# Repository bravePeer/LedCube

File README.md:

# LedCube
My version of Led Cube 5x5x5.

## Features:

| Name                     | Progress |
| :--:                     | :------: |
| animated letter          | in progress  |
| animation "droping leds" | in progress |
| animation with music     | planned |
| clock                    | planned |
| communication with PC    | in progress |

⚠️ Now all code is written to 5x5 led matrix.

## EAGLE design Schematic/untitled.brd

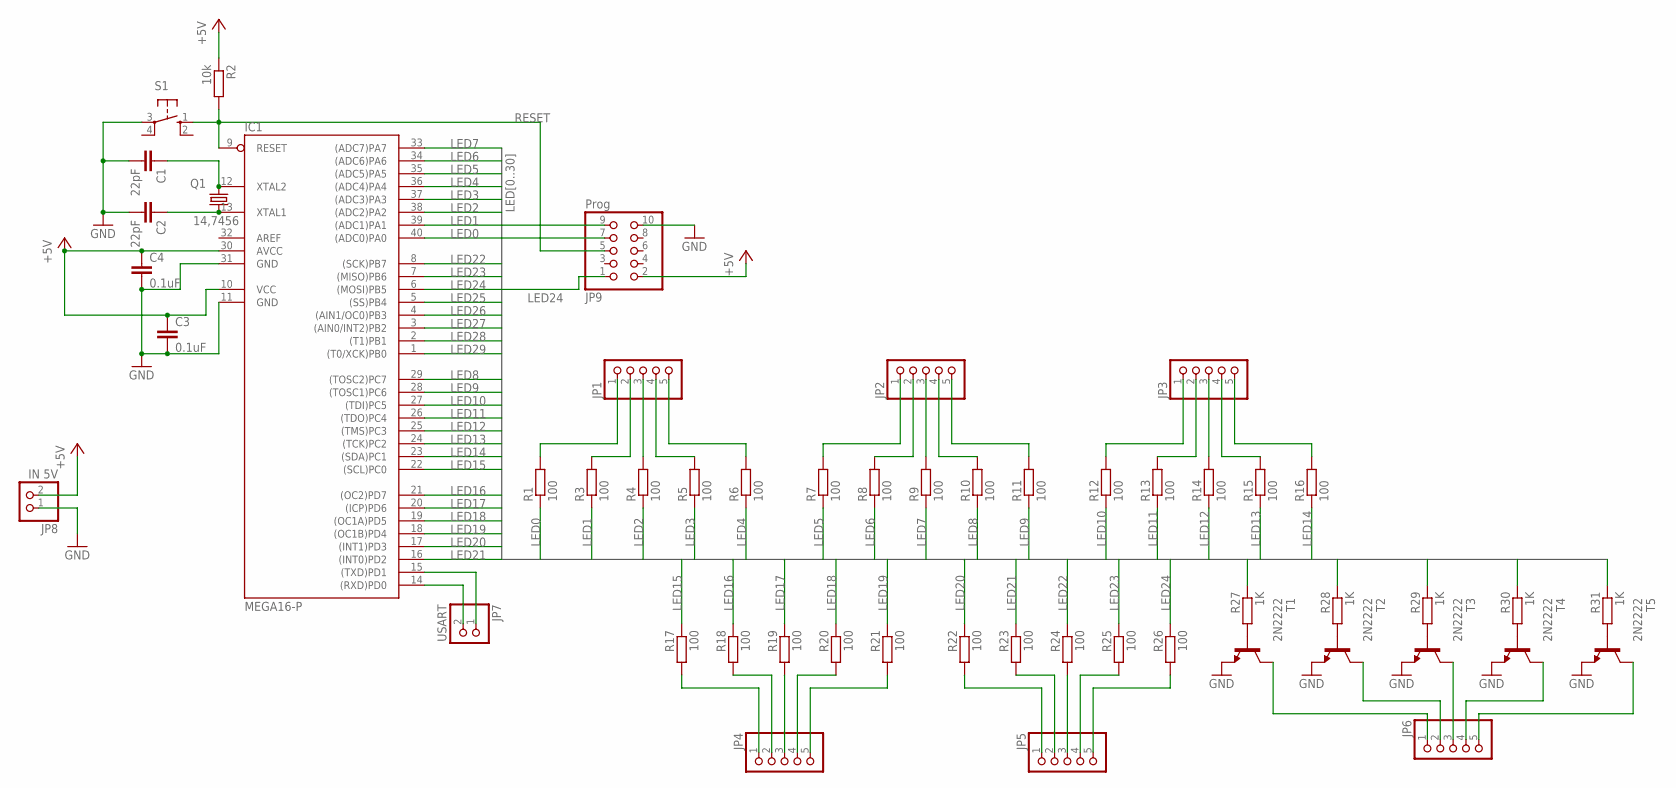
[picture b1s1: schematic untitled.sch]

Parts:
C1, C2: 22pF; C025-025X050
C3, C4: 0.1uF; C025-025X050
IC1: MEGA16-P; DIL40
JP1, JP2, JP3, JP4, JP5, JP6: PINHD-1X5; 1X05
JP7: USART; 1X02/90
JP8: IN 5V; 1X02/90
JP9: Prog; 2X05
Q1: 14,7456; HC49/S
R1, R3, R4, R5, R6, R7, R8, R9, R10, R11, R12, R13, R14, R15, R16, R17, R18, R19, R20, R21, R22, R23, R24, R25, R26: 100; 0207/7
R2: 10k; 0207/7
R27, R28, R29, R30, R31: 1K; 0207/7
S1: 10-XX; B3F-10XX
T1, T2, T3, T4, T5: 2N2222; TO18

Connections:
+5V: C3.1, C4.1, IC1.10 (VCC), IC1.30 (AVCC), JP8.2, JP9.2, R2.1
GND: C1.2, C2.2, C3.2, C4.2, IC1.11 (GND), IC1.31 (GND), JP8.1, JP9.10, S1.3, T1.1 (E), T2.1 (E), T3.1 (E), T4.1 (E), T5.1 (E)
LED0: IC1.40 ((ADC0)PA0), R1.1
LED1: IC1.39 ((ADC1)PA1), R3.1
LED2: IC1.38 ((ADC2)PA2), R4.1
LED3: IC1.37 ((ADC3)PA3), R5.1
LED4: IC1.36 ((ADC4)PA4), R6.1
LED5: IC1.35 ((ADC5)PA5), R7.1
LED6: IC1.34 ((ADC6)PA6), R8.1
LED7: IC1.33 ((ADC7)PA7), R9.1
LED8: IC1.29 ((TOSC2)PC7), R10.1
LED9: IC1.28 ((TOSC1)PC6), R11.1
LED10: IC1.27 ((TDI)PC5), R12.1
LED11: IC1.26 ((TDO)PC4), R13.1
LED12: IC1.25 ((TMS)PC3), R14.1
LED13: IC1.24 ((TCK)PC2), R15.1
LED14: IC1.23 ((SDA)PC1), R16.1
LED15: IC1.22 ((SCL)PC0), R17.1
LED16: IC1.21 ((OC2)PD7), R18.1
LED17: IC1.20 ((ICP)PD6), R19.1
LED18: IC1.19 ((OC1A)PD5), R20.1
LED19: IC1.18 ((OC1B)PD4), R21.1
LED20: IC1.17 ((INT1)PD3), R22.1
LED21: IC1.16 ((INT0)PD2), R23.1
LED22: IC1.8 ((SCK)PB7), JP9.7, R24.1
LED23: IC1.7 ((MISO)PB6), JP9.9, R25.1
LED24: IC1.6 ((MOSI)PB5), JP9.1, R26.1
LED25: IC1.5 ((SS)PB4), R27.1
LED26: IC1.4 ((AIN1/OC0)PB3), R28.1
LED27: IC1.3 ((AIN0/INT2)PB2), R29.1
LED28: IC1.2 ((T1)PB1), R30.1
LED29: IC1.1 ((T0/XCK)PB0), R31.1
unnamed: JP1.3, R4.2
unnamed: JP1.4, R5.2
unnamed: JP1.5, R6.2
unnamed: JP1.2, R3.2
unnamed: JP1.1, R1.2
unnamed: JP2.3, R9.2
unnamed: JP2.4, R10.2
unnamed: JP2.2, R8.2
unnamed: JP2.5, R11.2
unnamed: JP2.1, R7.2
unnamed: JP3.3, R14.2
unnamed: JP3.4, R15.2
unnamed: JP3.2, R13.2
unnamed: JP3.5, R16.2
unnamed: JP3.1, R12.2
unnamed: JP4.3, R19.2
unnamed: JP4.4, R20.2
unnamed: JP4.2, R18.2
unnamed: JP4.5, R21.2
unnamed: JP4.1, R17.2
unnamed: JP5.3, R24.2
unnamed: JP5.4, R25.2
unnamed: JP5.2, R23.2
unnamed: JP5.5, R26.2
unnamed: JP5.1, R22.2
unnamed: JP6.4, T4.3 (C)
unnamed: JP6.5, T5.3 (C)
unnamed: JP6.3, T3.3 (C)
unnamed: JP6.2, T2.3 (C)
unnamed: JP6.1, T1.3 (C)
unnamed: IC1.14 ((RXD)PD0), JP7.2
unnamed: IC1.15 ((TXD)PD1), JP7.1
unnamed: C1.1, IC1.12 (XTAL2), Q1.2
unnamed: C2.1, IC1.13 (XTAL1), Q1.1
unnamed: R27.2, T1.2 (B)
unnamed: R28.2, T2.2 (B)
unnamed: R29.2, T3.2 (B)
unnamed: R30.2, T4.2 (B)
unnamed: R31.2, T5.2 (B)
RESET: IC1.9 (RESET), JP9.5, R2.2, S1.1 (S)

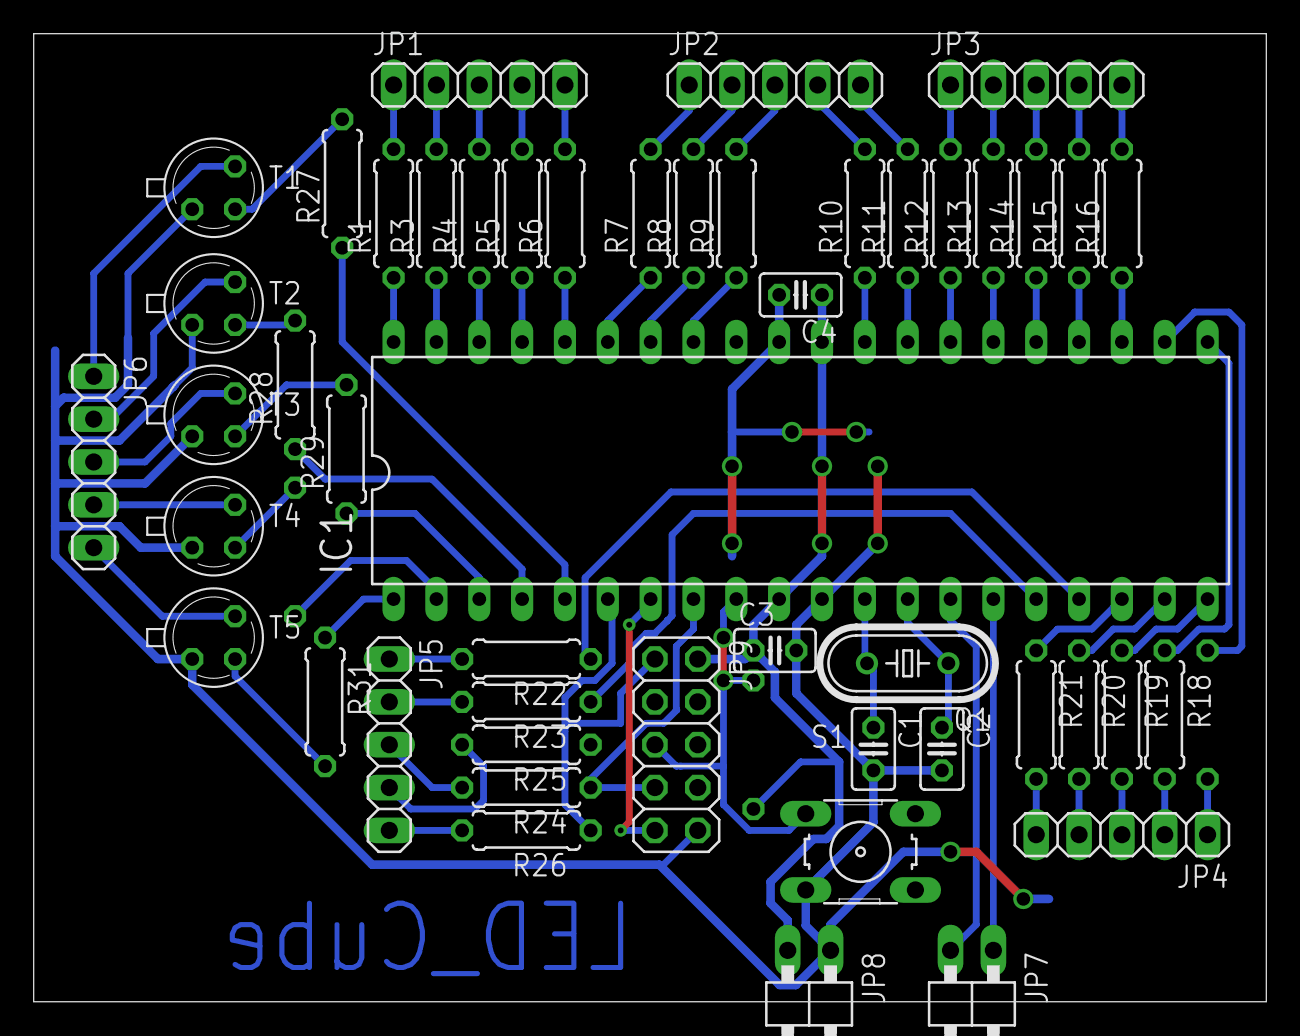
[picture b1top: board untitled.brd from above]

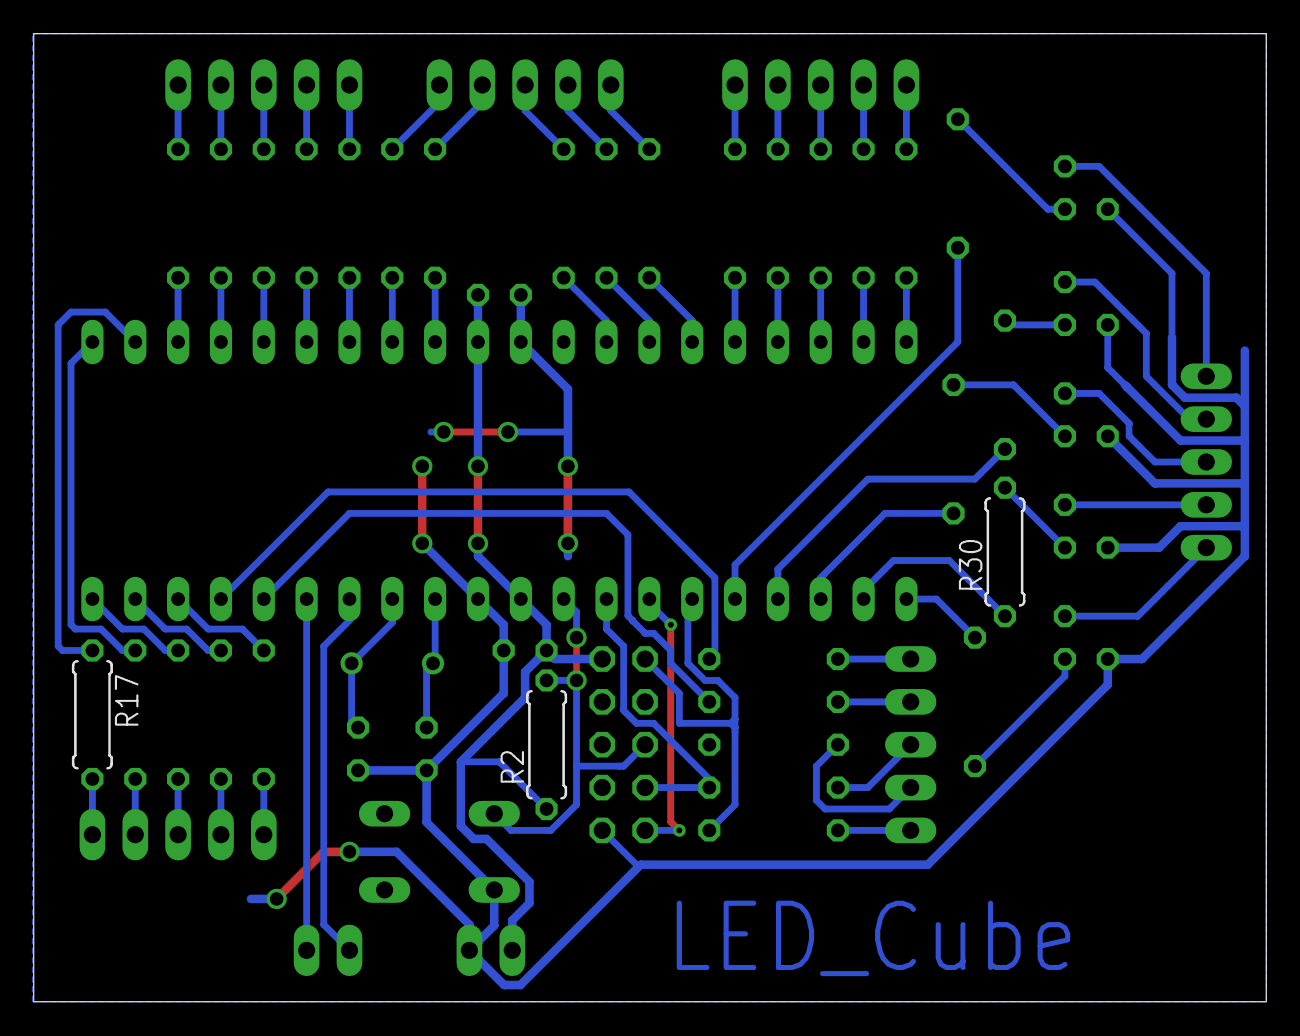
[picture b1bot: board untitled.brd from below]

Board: 2 copper layers, 73.1 x 57.4 mm, 52 parts (3 on the bottom side), 72 nets.

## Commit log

2022-04-30 Add current progress of my work.
